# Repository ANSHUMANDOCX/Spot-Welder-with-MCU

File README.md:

# Spot Welder with MCU
## Description
- This is a Mosfet Based Spot welder made using IRFB7430 mosfet paired with a OLED display, rotary encoder and ATMEGA328P IC. This is a projet inspired by [This Project](https://www.instructables.com/DIY-Arduino-Battery-Spot-Welder/) 
- This is a two PCB Design and made such that one can order the PCB as a whole and has to separate the PCBs by Cutting manually to save cost.
- It has two Aluminum parts that attach to the PCB since the circuit will be dealing high current of about 400A in a single pulse
- The pulse timing can be adjusted using the rotary encode and is very simple to use.
- It has a onboard programmer for the ease of programming the board
- Flash using Arduino IDE with ATmega328P bootloader and 9600 baud rate
- The Code is not tested yet on my design
## Parts used 
- IRFB7430 Mosfet
- Atmega328p as the MCU 
- 0.96 128x64 oled display
- ABR-PR-12APBTX90 Amaron 12v 9Ah Battey for high short pulse current
- 6AWG wire to handle the high current
- 4010 fan 
- 2mm solid copper wire
## Usage guide 
We need to connect the GND of the Battery from the IN sign and connect to the U shaped aluminium portion followed by the rectangular aluminium block as one of the probes the other probe will the positive terminal of the battery.
## PCB Schematic and CAD 

## Build 

https://drive.google.com/file/d/1lwMrrw48pk1E9WbPoM3kms2gutVuB4EL/view?usp=sharing

## BOM 
| Name                      | Purpose                         | Cost Per Item (USD) | Quantity | Total (USD) | Link | Distributor     |
|---------------------------|---------------------------------|---------------------|----------|-------------|------|-----------------|
| SHIPPING JLC+LCSC         | SHIPPING                        | 10.00               | 1        | 10.00       | [LINK](https://lcsc.com) | LCSC, JLC       |
| Aluminum parts+ PCB       | PCB + Aluminum Block            | 6.00                | 1        | 6.00        | [LINK](https://jlccnc.com) | JLCCNC, JLCPCB  |
| FAN                       | to disspate heat                | 0.70                | 1        | 0.70        | [LINK](https://makerbazar.in/products/generic-axial-dc-cooling-fan-blowers?variant=46306240004336) | Maker Bazar     |
| Passive Component         | Resistor diodes and Capacitor   | 6.06                | 1        | 6.06        | [LINK](https://lcsc.com) | LCSC            |
| 6AWG wire                 | Heavy duty wires                | 4.73                | 1        | 4.73        | [LINK](https://makerbazar.in/products/flexible-silicon-wire?variant=45564209725680&country=IN&currency=INR&gad_campaignid=17426677322) | Maker Bazar     |
| Battery 9ah               | the battery                     | 18.25               | 1        | 18.25       | [LINK](https://www.flipkart.com/amaron-abr-pr-12apbtx90-9-ah-battery-bike/p/itmd23986a4bee47?pid=VEBGSMF6ZHXYFG7V&lid=LSTVEBGSMF6ZHXYFG7VQWILCD&marketplace=FLIPKART&cmpid=content_vehicle-battery_22371611432_x_8965229628_gmc_pla&tgi=sem,1,G,11214002,x,,,,,,,c,,,,,,,&entryMethod=22371611432&&cmpid=content_22371611432_gmc_pla&gad_campaignid=22371673895) | Flipkart        |
| MCP1407-E/SN              | gate driver                     | 1.75                | 1        | 1.75        | [LINK](https://www.lcsc.com/product-detail/C52138.html) | LCSC            |
| 5.0SMDJ13A                | diode                           | 0.42                | 4        | 1.70        | [LINK](https://www.lcsc.com/product-detail/C5295091.html) | LCSC            |
| IRFB7430PBF(UMW)          | Mosfets                         | 0.44                | 10       | 4.43        | [LINK](https://www.lcsc.com/product-detail/C19100591.html) | LCSC            |
| CH340K                    | USB UART                        | 0.62                | 1        | 0.62        | [LINK](https://www.lcsc.com/product-detail/C968586.html) | LCSC            |
| Oled                      | to show the timer               | 2.17                | 1        | 2.17        | [LINK](https://www.lcsc.com/product-detail/C5248080.html) | LCSC            |
| Rotary encoder            | to set the timer                | 1.42                | 1        | 1.42        | [LINK](https://www.lcsc.com/product-detail/C19712528.html) | LCSC            |
| 3.3uH 20mΩ Inductor       | Inductor                        | 0.71                | 1        | 0.71        | [LINK](https://www.lcsc.com/product-detail/C7588932.html) | LCSC            |
| TPS563201DDCT             | Regulator                       | 0.46                | 1        | 0.46        | [LINK](https://www.lcsc.com/product-detail/C2070819.html) | LCSC            |
| ATMEGA328P-AU             | MCU                             | 2.17                | 1        | 2.17        | [LINK](https://www.lcsc.com/product-detail/C14877.html) | LCSC            |
| **Grand Total**           |                                 |                     |          | **63.17**   |      |                 |

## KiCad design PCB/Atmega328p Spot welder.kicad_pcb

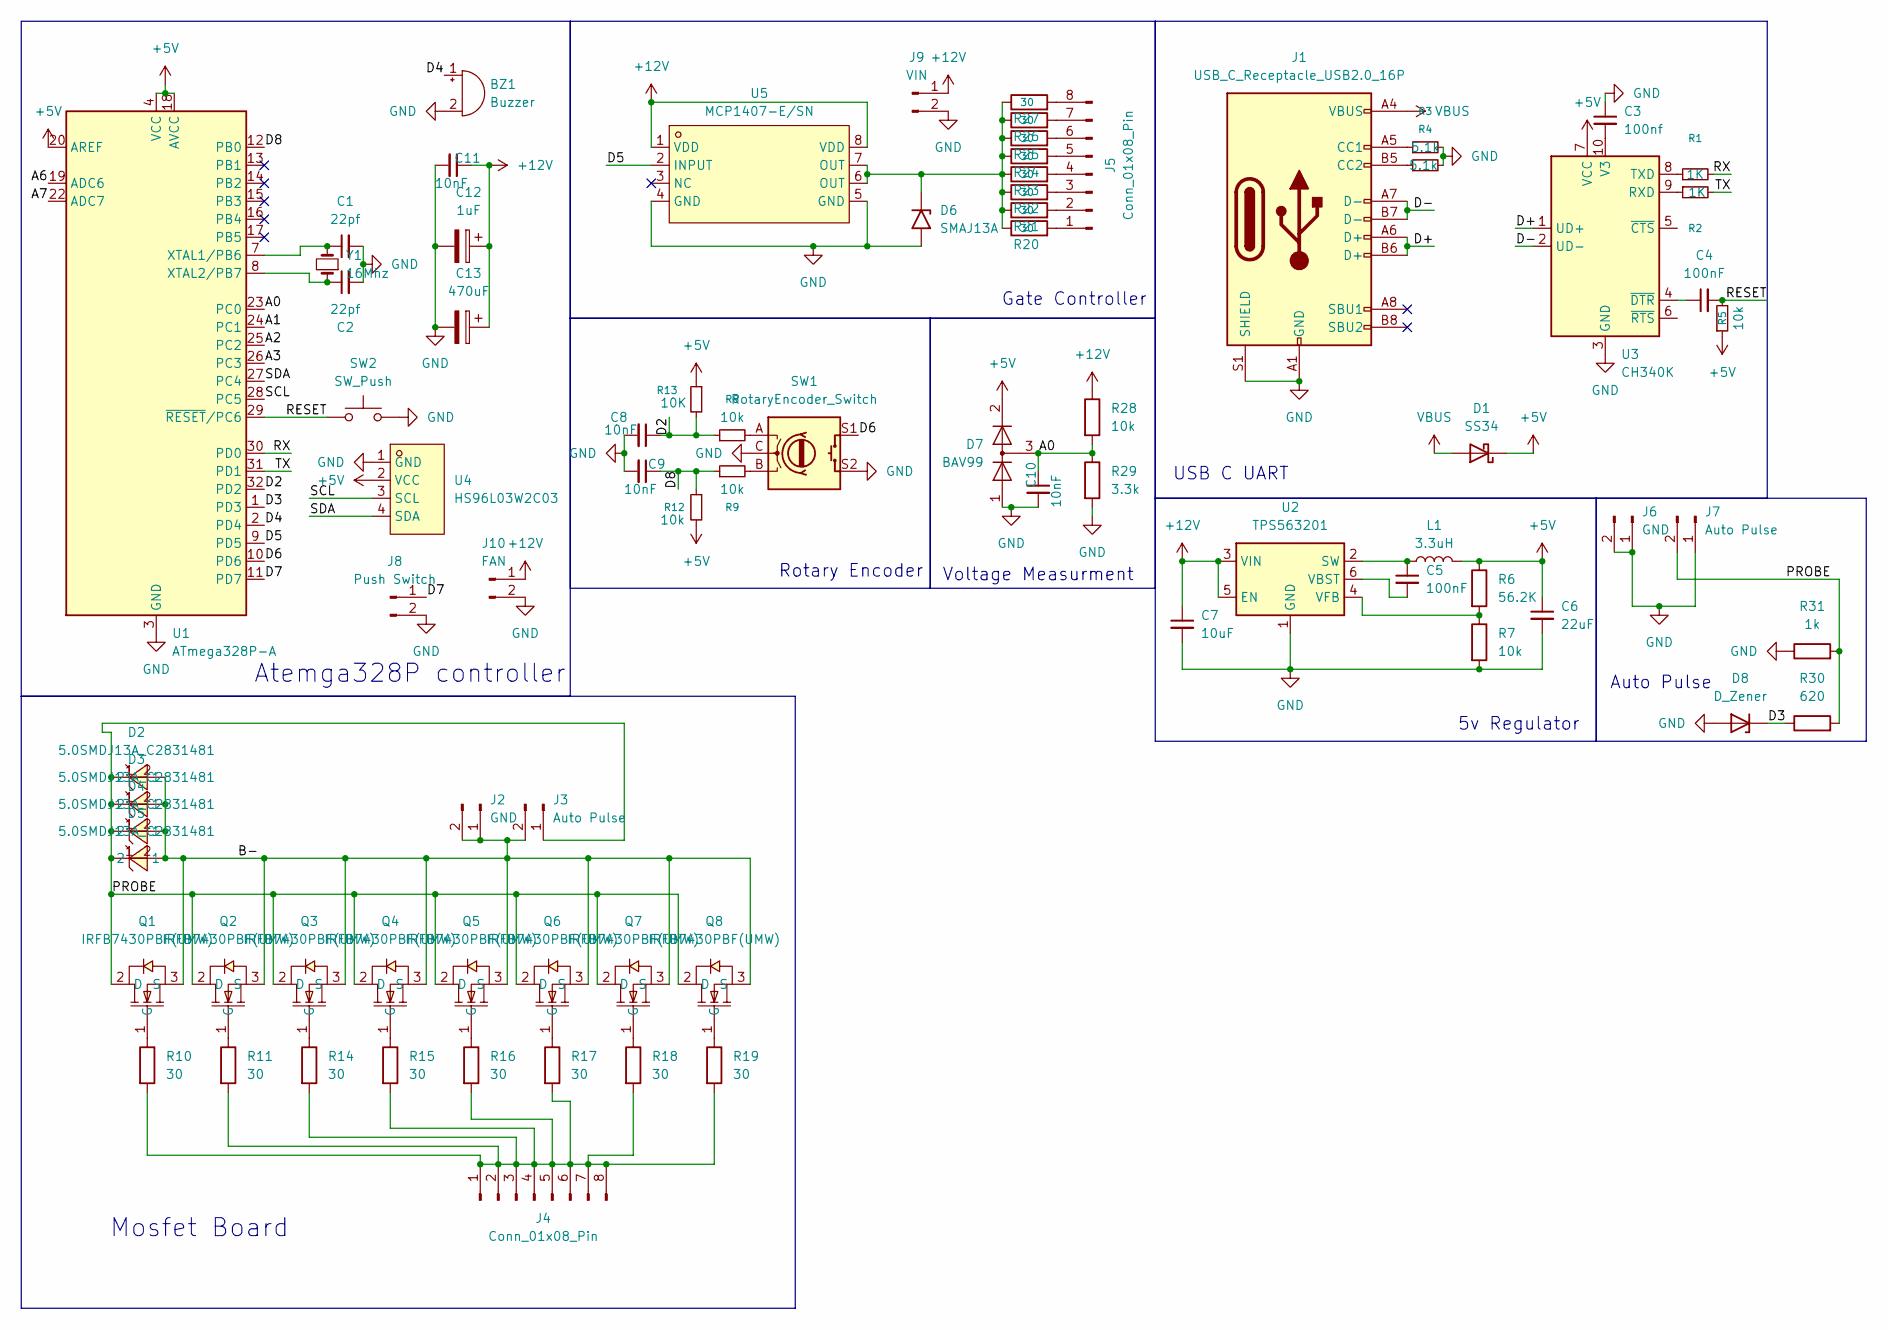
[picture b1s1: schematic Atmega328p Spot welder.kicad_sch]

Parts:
BZ1: Buzzer; Buzzer_12x9.5RM7.6
C1, C2: 22pf; C_0603_1608Metric
C3: 100nf; C_0603_1608Metric
C4, C5: 100nF; C_0603_1608Metric
C6: 22uF; C_0603_1608Metric
C7: 10uF; C_0603_1608Metric
C8, C9, C10, C11: 10nF; C_0603_1608Metric
C12: 1uF; CP_Elec_4x5.4
C13: 470uF; CP_Elec_8x10.5
D1: SS34; D_SMA
D2, D3, D4, D5: 5.0SMDJ13A_C2831481; SMC_L6.9-W5.9-LS8.0-RD; LCSC Part C2831481
D6: SMAJ13A; D_SMA
D7: BAV99; SOT-23
D8: D_Zener; D_SOD-123
J1: USB_C_Receptacle_USB2.0_16P; USB_C_Receptacle_HCTL_HC-TYPE-C-16P-01A
J2, J6: GND; PinHeader_1x02_P2.54mm_Vertical
J3, J7: Auto Pulse; PinHeader_1x02_P2.54mm_Vertical
J4, J5: Conn_01x08_Pin; PinHeader_1x08_P2.54mm_Vertical
J8: Push Switch; PinHeader_1x02_P2.54mm_Vertical
J9: VIN; PinHeader_1x02_P2.54mm_Vertical
J10: FAN; PinHeader_1x02_P2.54mm_Vertical
L1: 3.3uH; L_Bourns_SRP7028A_7.3x6.6mm
Q1, Q2, Q3, Q4, Q5, Q6, Q7, Q8: IRFB7430PBF(UMW); TO-220-3_Horizontal_TabDown; LCSC Part C19100591
R1, R2: 1K; C_0603_1608Metric
R3, R4: 5.1k; C_0603_1608Metric
R5, R7, R8, R9, R12, R28: 10k; C_0603_1608Metric
R6: 56.2K; C_0603_1608Metric
R10, R11, R14, R15, R16, R17, R18, R19, R20, R21, R22, R23, R24, R25, R26, R27: 30; R_1206_3216Metric
R13: 10K; C_0603_1608Metric
R29: 3.3k; C_0603_1608Metric
R30: 620; C_0603_1608Metric
R31: 1k; C_0603_1608Metric
SW1: RotaryEncoder_Switch; RotaryEncoder_Alps_EC11E_Vertical_H20mm_CircularMountingHol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
SW2: SW_Push; SW_Push_SPST_NO_Alps_SKRK
U1: ATmega328P-A; TQFP-32_7x7mm_P0.8mm
U2: TPS563201; SOT-23-6
U3: CH340K; SSOP-10-1EP_3.9x4.9mm_P1mm_EP2.1x3.3mm
U4: HS96L03W2C03; OLED-TH_L27.8-W27.2-P2.54_C9900033791; LCSC Part C5248080
U5: MCP1407-E/SN; SOP-8_L4.9-W3.9-P1.27-LS6.0-BL; LCSC Part C52138
Y1: 16Mhz; Crystal_SMD_5032-2Pin_5.0x3.2mm

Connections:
+5V: C6.1, D1.1 (K), D7.2 (A), L1.2, R5.1, R6.1, R12.2, R13.1, U1.4 (VCC), U1.6 (VCC), U1.18 (AVCC), U1.20 (AREF), U3.7 (VCC), U4.2 (VCC)
+12V: C7.1, C11.1, C12.1, C13.1, J9.1, J10.1, R28.1, U2.3 (VIN), U2.5 (EN), U5.1 (VDD), U5.8 (VDD)
/A0: C10.1, D7.3 (K), R28.2, R29.1, U1.23 (PC0)
/A1: U1.24 (PC1)
/A2: U1.25 (PC2)
/A3: U1.26 (PC3)
/A6: U1.19 (ADC6)
/A7: U1.22 (ADC7)
/B-: D2.2, D3.2, D4.2, D5.2, J2.1, J2.2, J3.2, Q1.3 (S), Q2.3 (S), Q3.3 (S), Q4.3 (S), Q5.3 (S), Q6.3 (S), Q7.3 (S), Q8.3 (S)
/D2: C8.1, R8.1, R13.2, U1.32 (PD2)
/D3: D8.1 (K), R30.1, U1.1 (PD3)
/D4: BZ1.1 (+), U1.2 (PD4)
/D5: U1.9 (PD5), U5.2 (INPUT)
/D6: SW1.S1, U1.10 (PD6)
/D7: J8.1, U1.11 (PD7)
/D8: C9.1, R9.1, R12.1, U1.12 (PB0)
/D+: J1.A6 (D+), J1.B6 (D+), U3.1 (UD+)
/D-: J1.A7 (D-), J1.B7 (D-), U3.2 (UD-)
/PROBE: D2.1, D3.1, D4.1, D5.1, J3.1, J7.2, Q1.2 (D), Q2.2 (D), Q3.2 (D), Q4.2 (D), Q5.2 (D), Q6.2 (D), Q7.2 (D), Q8.2 (D), R30.2, R31.2
/RESET: C4.2, R5.2, SW2.1, U1.29 (~RESET/PC6)
/RX: R1.2, U1.30 (PD0)
/SCL: U1.28 (PC5), U4.3 (SCL)
/SDA: U1.27 (PC4), U4.4 (SDA)
/TX: R2.2, U1.31 (PD1)
GND: BZ1.2 (-), C1.2, C2.2, C3.1, C6.2, C7.2, C8.2, C9.2, C10.2, C11.2, C12.2, C13.2, D6.2 (A2), D7.1 (K), D8.2 (A), J1.A1 (GND), J1.A12 (GND), J1.B1 (GND), J1.B12 (GND), J1.S1 (SHIELD), J6.1, J6.2, J7.1, J8.2, J9.2, J10.2, R3.2, R4.2, R7.2, R29.2, R31.1, SW1.C, SW1.S2, SW2.2, U1.3 (GND), U1.5 (GND), U1.21 (GND), U2.1 (GND), U3.3 (GND), U3.11 (GND), U4.1 (GND), U5.4 (GND), U5.5 (GND)
unnamed: D6.1 (A1), R20.1, R21.1, R22.1, R23.1, R24.1, R25.1, R26.1, R27.1, U5.6 (OUT), U5.7 (OUT)
unnamed: J1.A5 (CC1), R3.1
unnamed: J1.B5 (CC2), R4.1
unnamed: J4.1, J4.2, J4.3, J4.4, J4.5, J4.6, J4.7, J4.8, R10.2, R11.2, R14.2, R15.2, R16.2, R17.2, R18.2, R19.2
unnamed: J5.1, R20.2
unnamed: J5.2, R21.2
unnamed: J5.3, R22.2
unnamed: J5.4, R23.2
unnamed: J5.5, R24.2
unnamed: J5.6, R25.2
unnamed: J5.7, R26.2
unnamed: J5.8, R27.2
unnamed: Q1.1 (G), R10.1
unnamed: Q2.1 (G), R11.1
unnamed: Q3.1 (G), R14.1
unnamed: Q4.1 (G), R15.1
unnamed: Q5.1 (G), R16.1
unnamed: Q6.1 (G), R17.1
unnamed: Q7.1 (G), R18.1
unnamed: Q8.1 (G), R19.1
unnamed: R8.2, SW1.A
unnamed: R9.2, SW1.B
unnamed: C1.1, U1.7 (XTAL1/PB6), Y1.2
unnamed: C2.1, U1.8 (XTAL2/PB7), Y1.1
unnamed: C5.1, L1.1, U2.2 (SW)
unnamed: C5.2, U2.6 (VBST)
unnamed: R6.2, R7.1, U2.4 (VFB)
unnamed: R2.1, U3.9 (RXD)
unnamed: R1.1, U3.8 (TXD)
unnamed: C3.2, U3.10 (V3)
unnamed: C4.1, U3.4 (~DTR)
VBUS: D1.2 (A), J1.A4 (VBUS), J1.A9 (VBUS), J1.B4 (VBUS), J1.B9 (VBUS)

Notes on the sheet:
5v Regulator
Rotary Encoder
Auto Pulse
Mosfet Board
Voltage Measurment
Gate Controller
USB C UART
Atemga328P controller

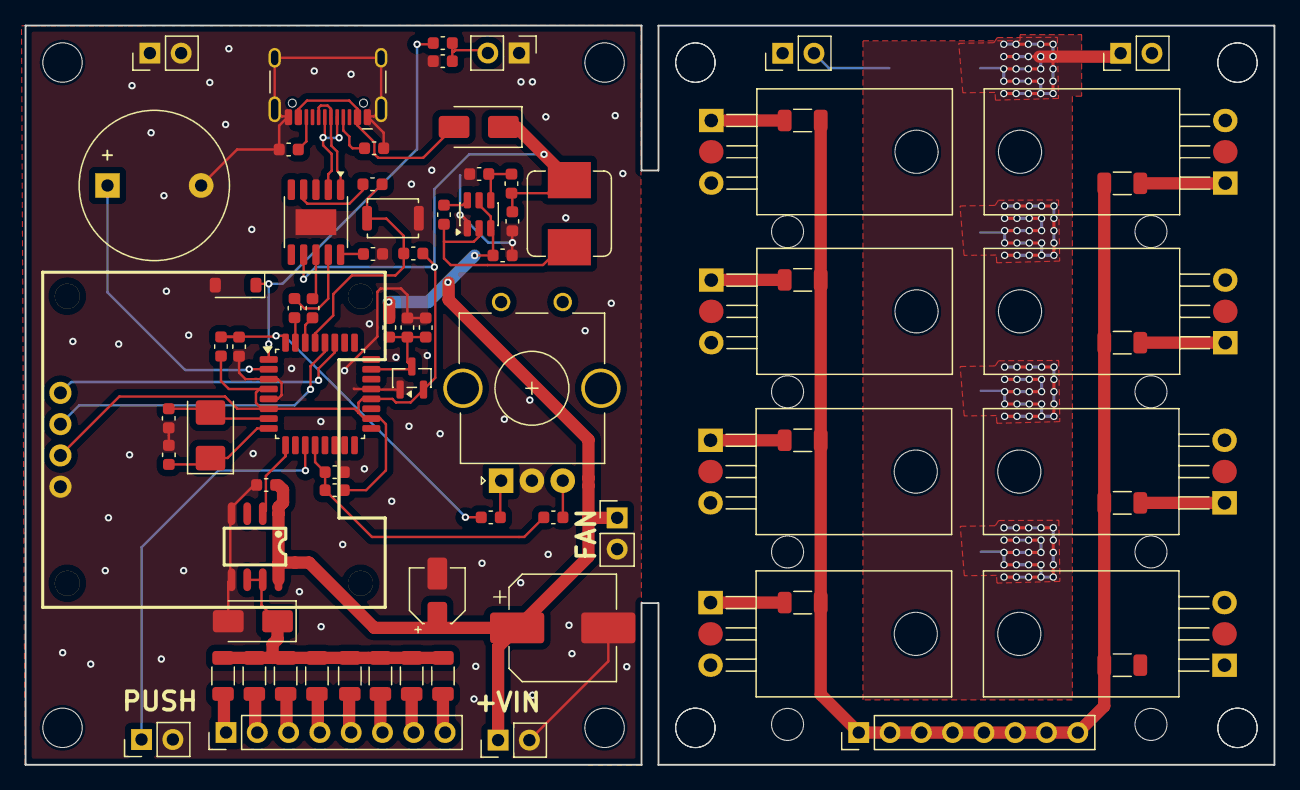
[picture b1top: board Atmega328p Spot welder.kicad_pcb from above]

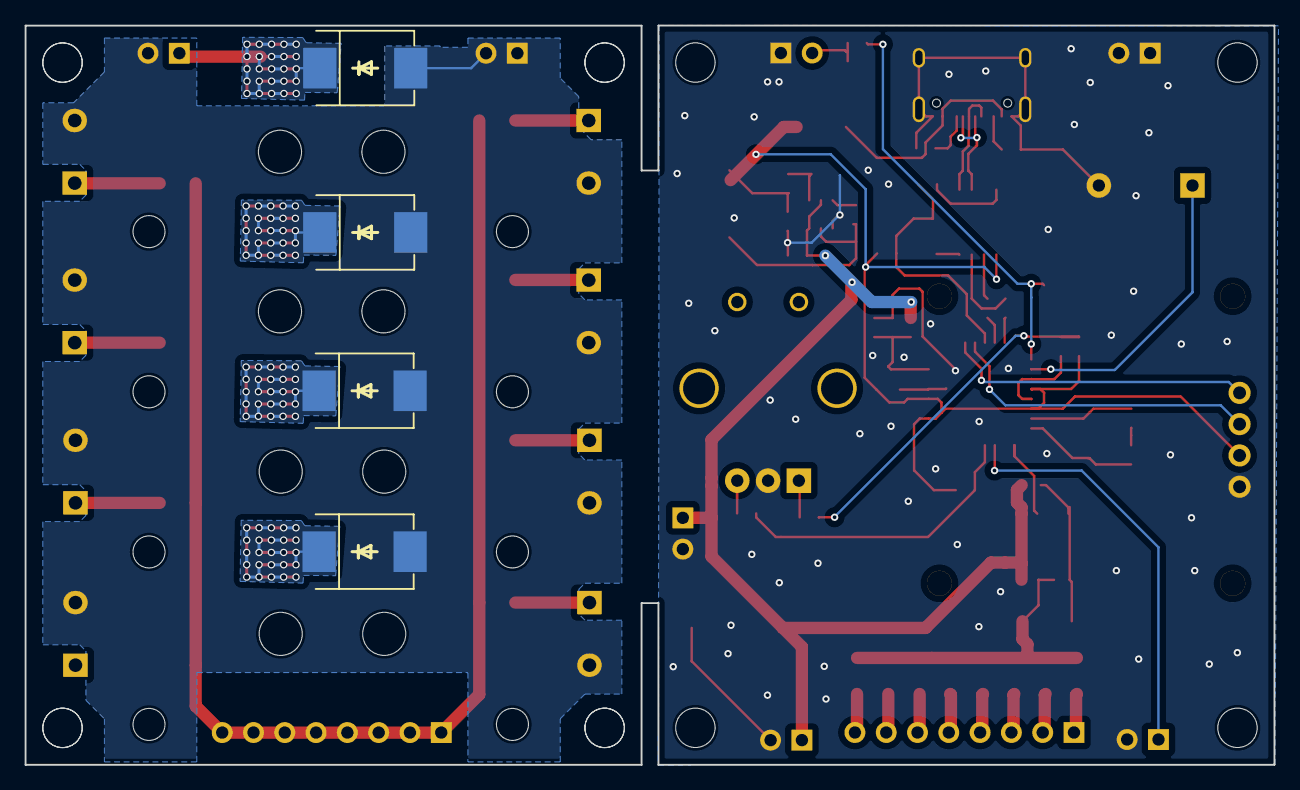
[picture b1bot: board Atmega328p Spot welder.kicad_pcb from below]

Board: 2 copper layers, 101.4 x 60.0 mm, 80 parts (4 on the bottom side), 51 nets.

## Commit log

2026-03-18 Update README with flashing instructions
    Added information about flashing the board using Arduino IDE.
